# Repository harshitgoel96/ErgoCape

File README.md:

# This project has been abandond in favour of Pteron36.
## ErgoCape
For the love of all beautiful keycaps

After struggling to get any decent set for ergodox, I decided it was better to shoehorn the ergodox layout to work with the keycaps, instead of getting specialised keycaps.

The pcb top would look something like this.

The pcb bottom would look something like this.

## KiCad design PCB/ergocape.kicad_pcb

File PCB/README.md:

# ErgoCape
104 ansi keycap friendly ergonomic split keyboard

After struggling to get any decent set for ergodox, I decided it was better to shoehorn the ergodox layout to work with the keycaps, instead of getting specialised keycaps.

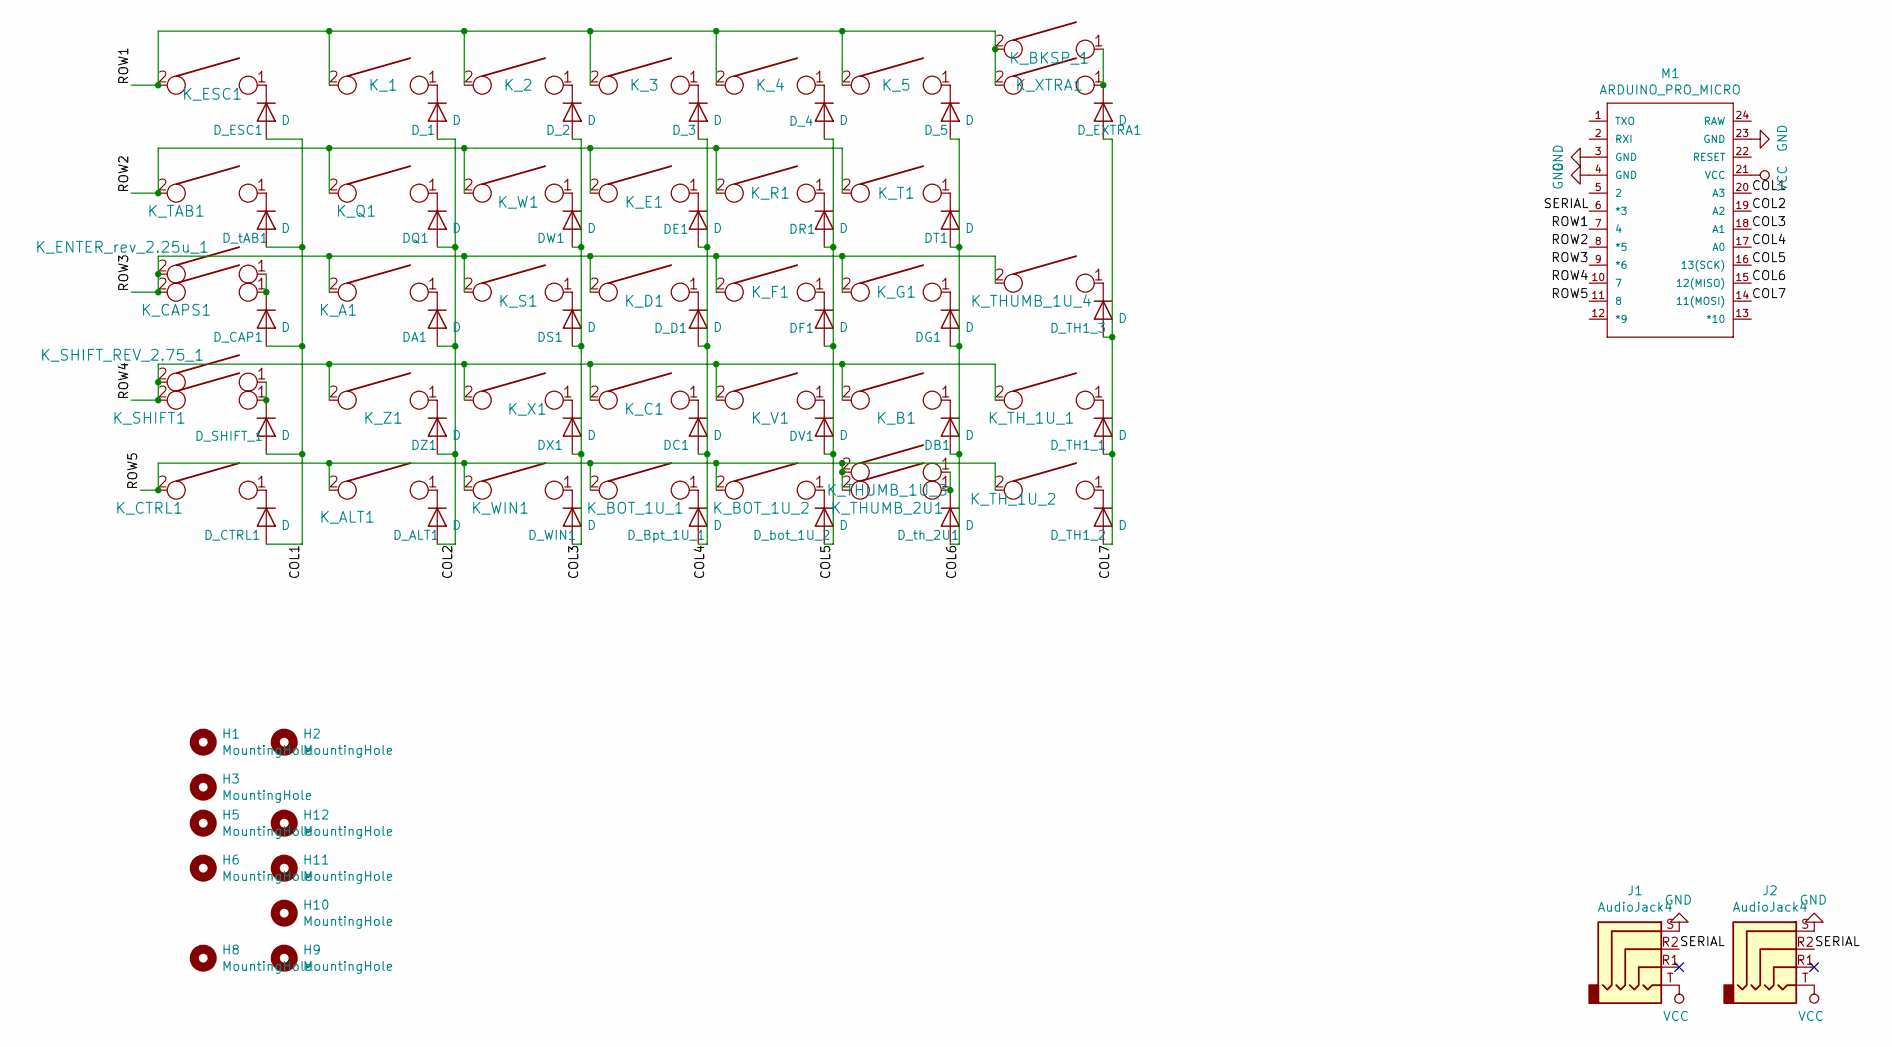
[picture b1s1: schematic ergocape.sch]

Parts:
DA1: D; Diode-dual
DB1: D; Diode-dual
DC1: D; Diode-dual
DE1: D; Diode-dual
DF1: D; Diode-dual
DG1: D; Diode-dual
DQ1: D; Diode-dual
DR1: D; Diode-dual
DS1: D; Diode-dual
DT1: D; Diode-dual
DV1: D; Diode-dual
DW1: D; Diode-dual
DX1: D; Diode-dual
DZ1: D; Diode-dual
D_1, D_2, D_3, D_4, D_5: D; Diode-dual
D_ALT1: D; Diode-dual
D_Bpt_1U_1: D; Diode-dual
D_CAP1: D; Diode-dual
D_CTRL1: D; Diode-dual
D_D1: D; Diode-dual
D_ESC1: D; Diode-dual
D_EXTRA1: D; Diode-dual
D_SHIFT_1: D; Diode-dual
D_TH1_1, D_TH1_2, D_TH1_3: D; Diode-dual
D_WIN1: D; Diode-dual
D_bot_1U_2: D; Diode-dual
D_tAB1: D; Diode-dual
D_th_2U1: D; Diode-dual
H1, H2, H3, H5, H6, H8, H9, H10, H11, H12: MountingHole; MountingHole_2.5x4.0mm
J1, J2: AudioJack4; TRRS-PJ-320D_PAD
K_1, K_2, K_3, K_4, K_5: KEYSW; Hybrid_PCB_100H_Dual_hole
K_A1: KEYSW; Hybrid_PCB_100H_Dual_hole
K_ALT1: KEYSW; Hybrid_PCB_100H_Dual_hole
K_B1: KEYSW; Hybrid_PCB_100H_Dual_hole
K_BKSP_1: KEYSW; Hybrid_PCB_200H-dual
K_BOT_1U_1, K_BOT_1U_2: KEYSW; Hybrid_PCB_100H_Dual_hole
K_C1: KEYSW; Hybrid_PCB_100H_Dual_hole
K_CAPS1: KEYSW; Hybrid_PCB_175H
K_CTRL1: KEYSW; Hybrid_PCB_100H_Dual_hole
K_D1: KEYSW; Hybrid_PCB_100H_Dual_hole
K_E1: KEYSW; Hybrid_PCB_100H_Dual_hole
K_ENTER_rev_2.25u_1: KEYSW; Hybrid_PCB_225H
K_ESC1: KEYSW; Hybrid_PCB_100H_Dual_hole
K_F1: KEYSW; Hybrid_PCB_100H_Dual_hole
K_G1: KEYSW; Hybrid_PCB_100H_Dual_hole
K_Q1: KEYSW; Hybrid_PCB_100H_Dual_hole
K_R1: KEYSW; Hybrid_PCB_100H_Dual_hole
K_S1: KEYSW; Hybrid_PCB_100H_Dual_hole
K_SHIFT1: KEYSW; Hybrid_PCB_225H
K_SHIFT_REV_2.75_1: KEYSW; Hybrid_PCB_275H
K_T1: KEYSW; Hybrid_PCB_100H_Dual_hole
K_TAB1: KEYSW; Hybrid_PCB_150H_Dual_hole
K_THUMB_1U_3, K_THUMB_1U_4: KEYSW; Hybrid_PCB_100H_Dual_hole
K_THUMB_2U1: KEYSW; Hybrid_PCB_200H-dual-nosilk
K_TH_1U_1, K_TH_1U_2: KEYSW; Hybrid_PCB_100H_Dual_hole
K_V1: KEYSW; Hybrid_PCB_100H_Dual_hole
K_W1: KEYSW; Hybrid_PCB_100H_Dual_hole
K_WIN1: KEYSW; Hybrid_PCB_100H_Dual_hole
K_X1: KEYSW; Hybrid_PCB_100H_Dual_hole
K_XTRA1: KEYSW; Hybrid_PCB_100H_Dual_hole
K_Z1: KEYSW; Hybrid_PCB_100H_Dual_hole
M1: ARDUINO_PRO_MICRO

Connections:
/COL1: D_CAP1.2 (A), D_CTRL1.2 (A), D_ESC1.2 (A), D_SHIFT_1.2 (A), D_tAB1.2 (A), M1.20 (A3)
/COL2: DA1.2 (A), DQ1.2 (A), DZ1.2 (A), D_1.2 (A), D_ALT1.2 (A), M1.19 (A2)
/COL3: DS1.2 (A), DW1.2 (A), DX1.2 (A), D_2.2 (A), D_WIN1.2 (A), M1.18 (A1)
/COL4: DC1.2 (A), DE1.2 (A), D_3.2 (A), D_Bpt_1U_1.2 (A), D_D1.2 (A), M1.17 (A0)
/COL5: DF1.2 (A), DR1.2 (A), DV1.2 (A), D_4.2 (A), D_bot_1U_2.2 (A), M1.16 (13(SCK))
/COL6: DB1.2 (A), DG1.2 (A), DT1.2 (A), D_5.2 (A), D_th_2U1.2 (A), M1.15 (12(MISO))
/COL7: D_EXTRA1.2 (A), D_TH1_1.2 (A), D_TH1_2.2 (A), D_TH1_3.2 (A), M1.14 (11(MOSI))
/ROW1: K_1.2, K_2.2, K_3.2, K_4.2, K_5.2, K_BKSP_1.2, K_ESC1.2, K_XTRA1.2, M1.7 (4)
/ROW2: K_E1.2, K_Q1.2, K_R1.2, K_T1.2, K_TAB1.2, K_W1.2, M1.8 (*5)
/ROW3: K_A1.2, K_CAPS1.2, K_D1.2, K_ENTER_rev_2.25u_1.2, K_F1.2, K_G1.2, K_S1.2, K_THUMB_1U_4.2, M1.9 (*6)
/ROW4: K_B1.2, K_C1.2, K_SHIFT1.2, K_SHIFT_REV_2.75_1.2, K_TH_1U_1.2, K_V1.2, K_X1.2, K_Z1.2, M1.10 (7)
/ROW5: K_ALT1.2, K_BOT_1U_1.2, K_BOT_1U_2.2, K_CTRL1.2, K_THUMB_1U_3.2, K_THUMB_2U1.2, K_TH_1U_2.2, K_WIN1.2, M1.11 (8)
/SERIAL: J1.R2, J2.R2, M1.6 (*3)
GND: J1.S, J2.S, M1.3 (GND), M1.4 (GND), M1.23 (GND)
unnamed: DA1.1 (K), K_A1.1
unnamed: DB1.1 (K), K_B1.1
unnamed: DC1.1 (K), K_C1.1
unnamed: DE1.1 (K), K_E1.1
unnamed: DF1.1 (K), K_F1.1
unnamed: DG1.1 (K), K_G1.1
unnamed: DQ1.1 (K), K_Q1.1
unnamed: DR1.1 (K), K_R1.1
unnamed: DS1.1 (K), K_S1.1
unnamed: DT1.1 (K), K_T1.1
unnamed: DV1.1 (K), K_V1.1
unnamed: DW1.1 (K), K_W1.1
unnamed: DX1.1 (K), K_X1.1
unnamed: DZ1.1 (K), K_Z1.1
unnamed: D_1.1 (K), K_1.1
unnamed: D_2.1 (K), K_2.1
unnamed: D_3.1 (K), K_3.1
unnamed: D_4.1 (K), K_4.1
unnamed: D_5.1 (K), K_5.1
unnamed: D_ALT1.1 (K), K_ALT1.1
unnamed: D_Bpt_1U_1.1 (K), K_BOT_1U_1.1
unnamed: D_CAP1.1 (K), K_CAPS1.1, K_ENTER_rev_2.25u_1.1
unnamed: D_CTRL1.1 (K), K_CTRL1.1
unnamed: D_D1.1 (K), K_D1.1
unnamed: D_ESC1.1 (K), K_ESC1.1
unnamed: D_EXTRA1.1 (K), K_BKSP_1.1, K_XTRA1.1
unnamed: D_SHIFT_1.1 (K), K_SHIFT1.1, K_SHIFT_REV_2.75_1.1
unnamed: D_TH1_1.1 (K), K_TH_1U_1.1
unnamed: D_TH1_2.1 (K), K_TH_1U_2.1
unnamed: D_TH1_3.1 (K), K_THUMB_1U_4.1
unnamed: D_WIN1.1 (K), K_WIN1.1
unnamed: D_bot_1U_2.1 (K), K_BOT_1U_2.1
unnamed: D_tAB1.1 (K), K_TAB1.1
unnamed: D_th_2U1.1 (K), K_THUMB_1U_3.1, K_THUMB_2U1.1
VCC: J1.T, J2.T, M1.21 (VCC)

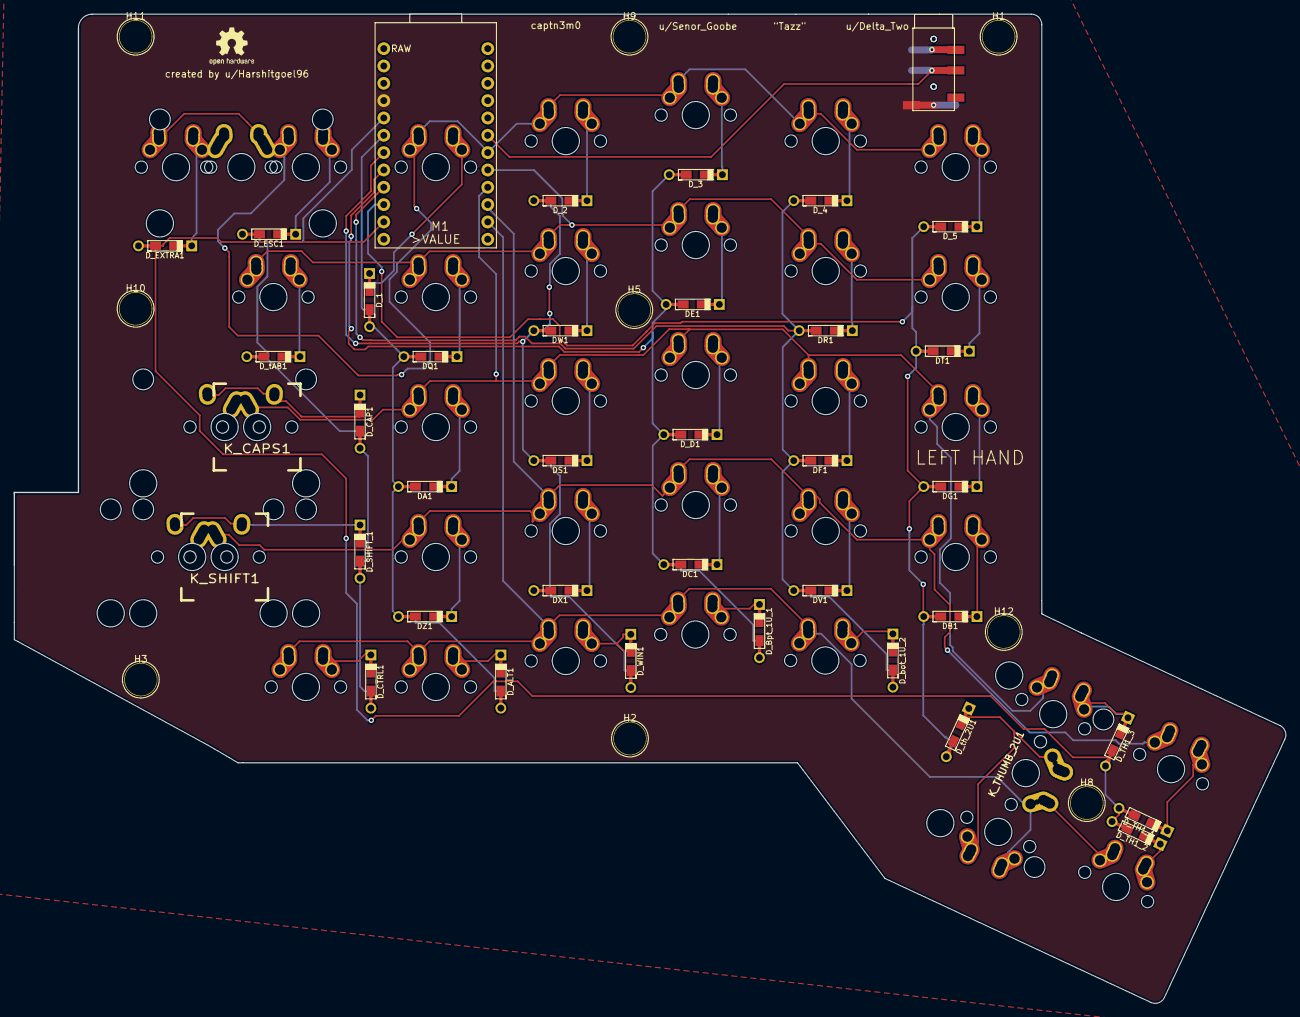
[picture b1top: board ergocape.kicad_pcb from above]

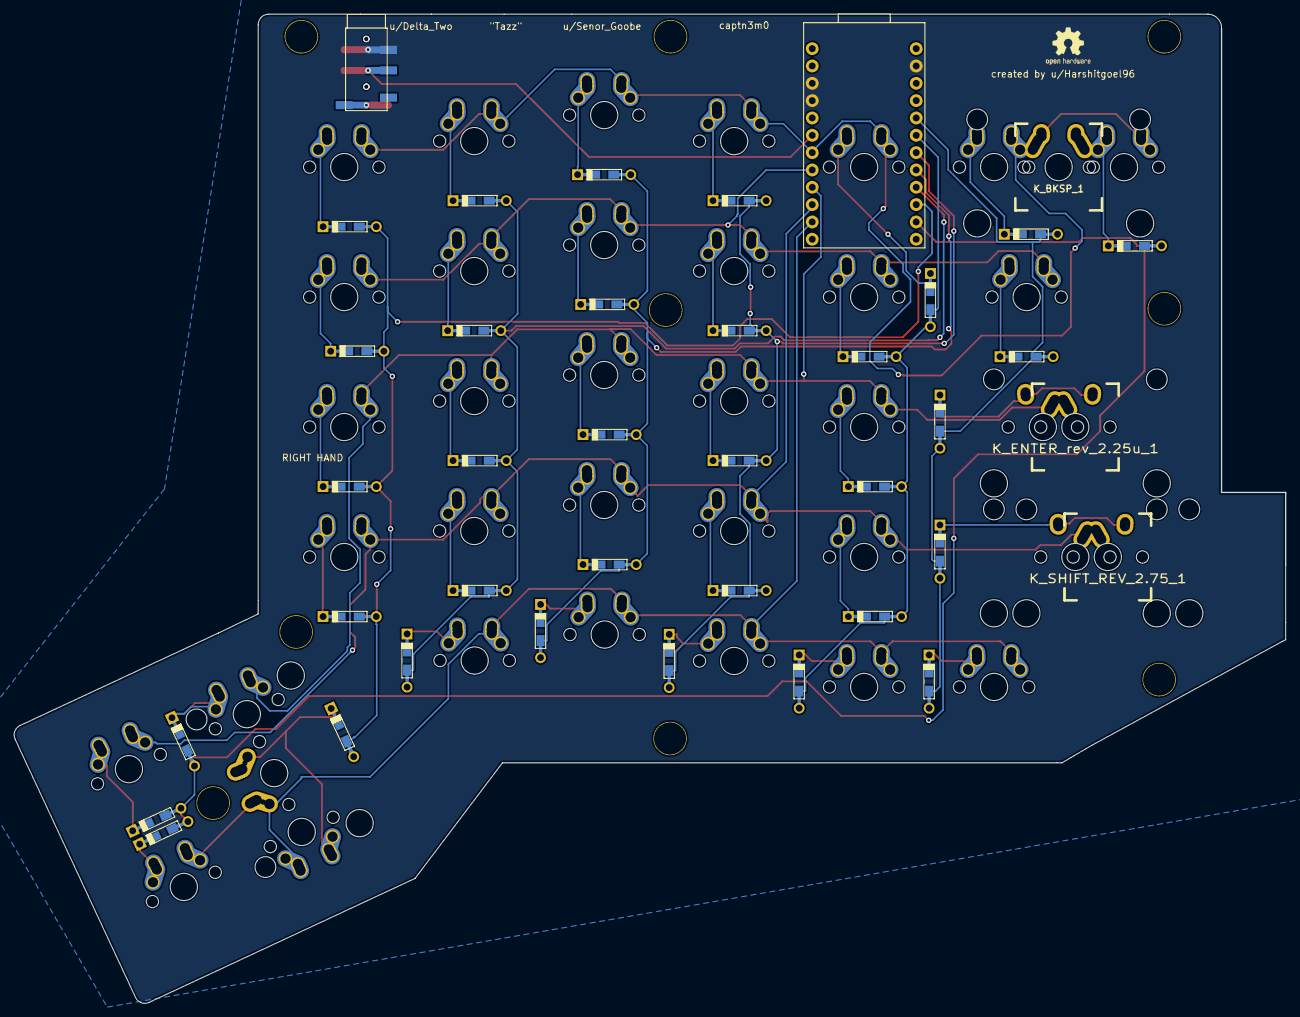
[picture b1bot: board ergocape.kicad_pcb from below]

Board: 2 copper layers, 186.4 x 145.0 mm, 86 parts (7 on the bottom side), 49 nets.

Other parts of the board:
log_bsilk1: OSHW-Logo2_7.3x6mm_SilkScreen
logo_fsilk: OSHW-Logo2_7.3x6mm_SilkScreen

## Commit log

2020-01-02 initial design commit
2020-01-02 commit pcb renders
2020-01-02 add license
2020-01-02 add layout image
2020-01-03 sparate out pcb and case files
2020-01-04 added files for case files based of fr4 or similar.
2020-01-15 Change in layout and design, remove atmega32u4
2020-01-15 cleanup
2020-01-16 cleanup and finish the case files
2020-01-16 add renders
2020-01-18 finalize plate and mounting holes
2020-01-18 release final design, added renders
2020-01-18 added svg image link
2020-03-03 cleanup some wiring, check diode placement
2020-06-21 fix pro micro footprint
